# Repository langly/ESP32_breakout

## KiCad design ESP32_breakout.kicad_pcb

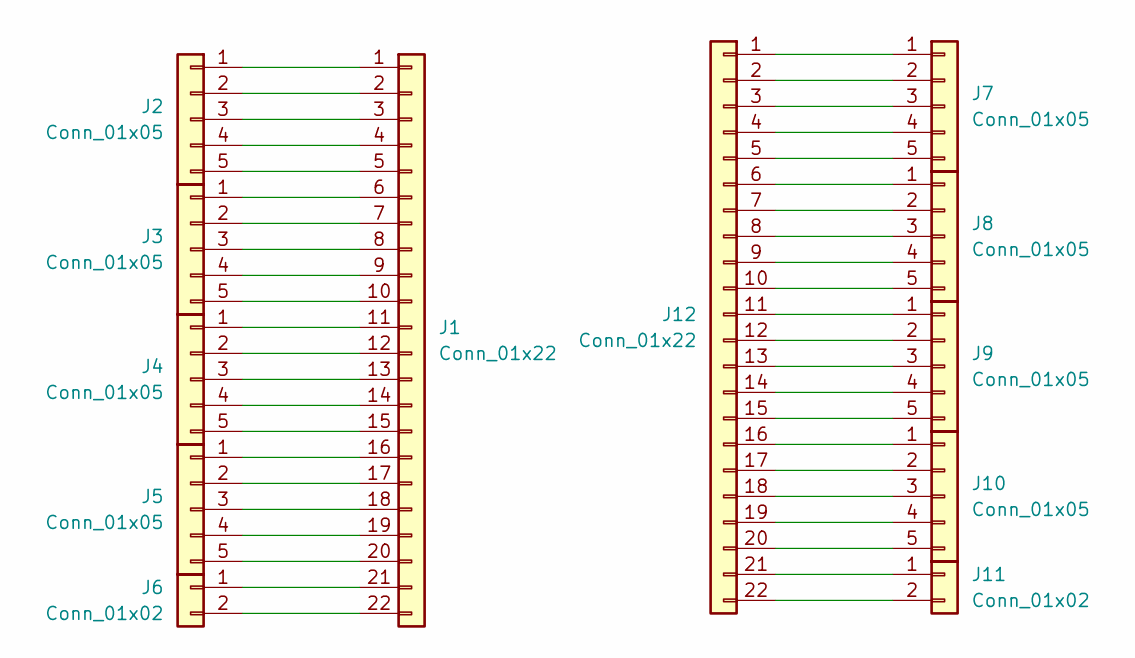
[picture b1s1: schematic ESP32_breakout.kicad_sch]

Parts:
J1, J12: Conn_01x22; PinHeader_1x22_P2.54mm_Vertical
J2, J3, J4, J5, J7, J8, J9, J10: Conn_01x05; TerminalBlock_TE_282834-5_1x05_P2.54mm_Horizontal
J6, J11: Conn_01x02; TerminalBlock_TE_282834-2_1x02_P2.54mm_Horizontal

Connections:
unnamed: J1.1, J2.1
unnamed: J1.2, J2.2
unnamed: J1.3, J2.3
unnamed: J1.4, J2.4
unnamed: J1.5, J2.5
unnamed: J1.6, J3.1
unnamed: J1.7, J3.2
unnamed: J1.8, J3.3
unnamed: J1.9, J3.4
unnamed: J1.10, J3.5
unnamed: J1.11, J4.1
unnamed: J1.12, J4.2
unnamed: J1.13, J4.3
unnamed: J1.14, J4.4
unnamed: J1.15, J4.5
unnamed: J1.16, J5.1
unnamed: J1.17, J5.2
unnamed: J1.18, J5.3
unnamed: J1.19, J5.4
unnamed: J1.20, J5.5
unnamed: J1.21, J6.1
unnamed: J1.22, J6.2
unnamed: J10.1, J12.16
unnamed: J10.2, J12.17
unnamed: J10.3, J12.18
unnamed: J10.4, J12.19
unnamed: J10.5, J12.20
unnamed: J11.1, J12.21
unnamed: J11.2, J12.22
unnamed: J7.1, J12.1
unnamed: J7.2, J12.2
unnamed: J7.3, J12.3
unnamed: J7.4, J12.4
unnamed: J7.5, J12.5
unnamed: J8.1, J12.6
unnamed: J8.2, J12.7
unnamed: J8.3, J12.8
unnamed: J8.4, J12.9
unnamed: J8.5, J12.10
unnamed: J9.1, J12.11
unnamed: J9.2, J12.12
unnamed: J9.3, J12.13
unnamed: J9.4, J12.14
unnamed: J9.5, J12.15

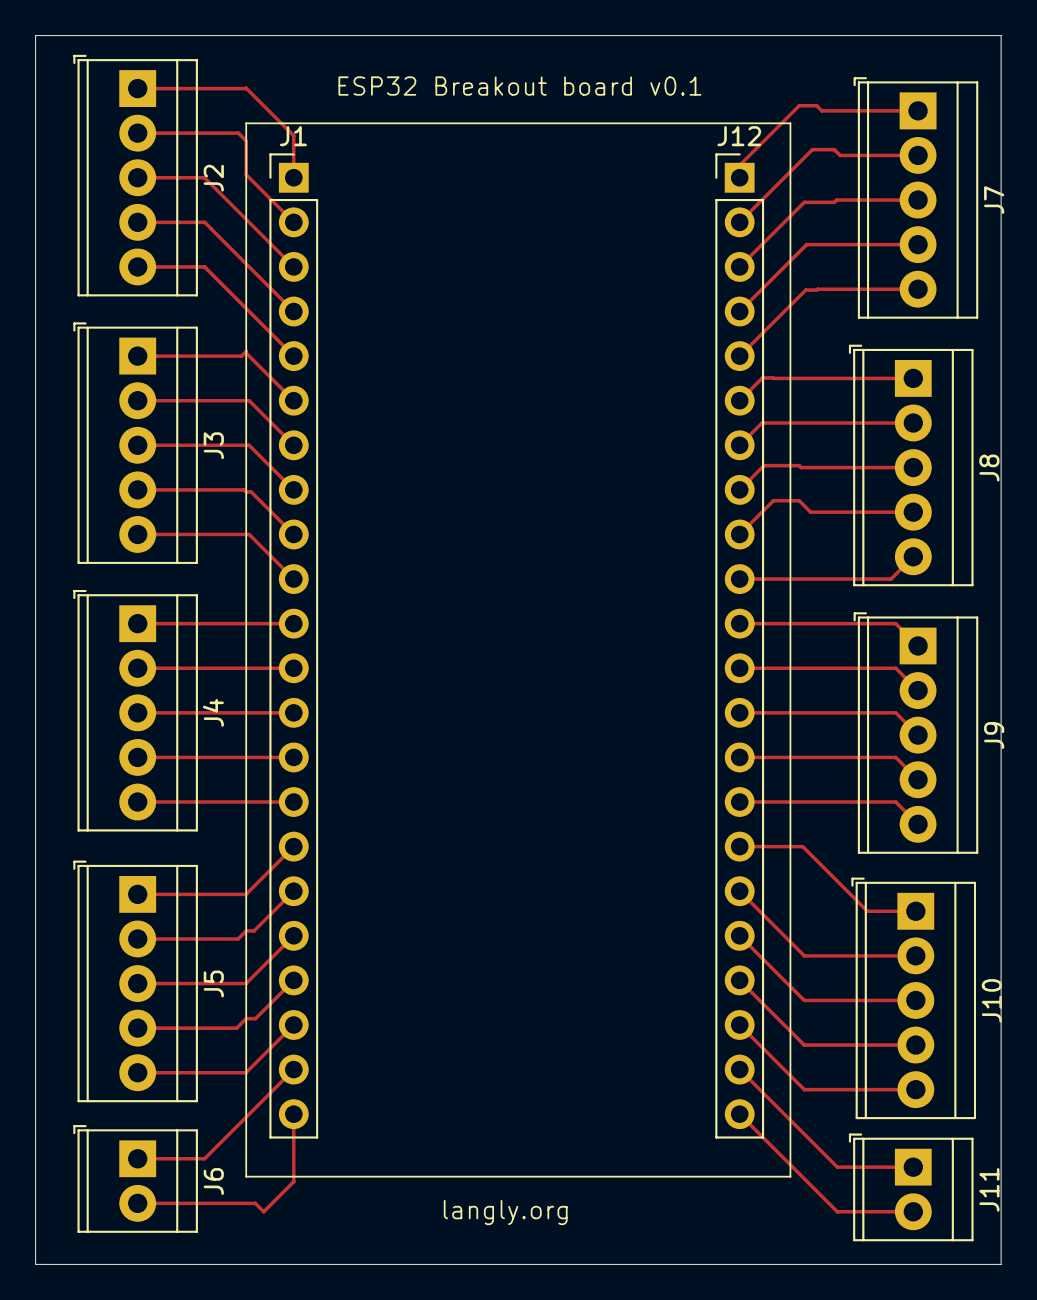
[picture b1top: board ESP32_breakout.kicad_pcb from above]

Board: 2 copper layers, 55.0 x 70.0 mm, 12 parts (0 on the bottom side), 44 nets.

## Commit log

2024-09-20 Initial checkin of the ESP32 Breakout board
